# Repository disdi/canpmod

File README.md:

# CAN PMOD

CAN PMOD is a 3.3 V SN65HVD230 CAN transceiver module, based on the
[Waveshare SN65HVD230 CAN board](https://www.waveshare.com/sn65hvd230-can-board.htm/).
The host must provide the CAN protocol controller.

The project is **KiCad 9.0.8**. Open [kicad/canpmod.kicad_pro](kicad/canpmod.kicad_pro).
The two-layer, 1.6 mm board has 12 components and keeps its original outline
and component placement.

This revision corrects the PMOD footprint's physical numbering, reroutes the
affected nets, adds local connector footprints, and refreshes silkscreen and
library symbols. ERC reports 0 errors and 0 warnings. DRC with schematic
parity reports 0 violations and 0 unconnected items.

The photographs above show the original board. They remain in `img/` as
historical images.

## PMOD connections

**J2** is the right-angle male PMOD header. Viewed from the PCB top with its
plug pointing left, pins 1–6 run top to bottom in the inboard row; pins 7–12
run top to bottom in the outboard row. Pin 1 is square and marked on silkscreen.

| PMOD pin | Signal | Function |
| --- | --- | --- |
| 1 | NC | Unconnected |
| 2 | NC | Unconnected |
| 3 | NC | Unconnected |
| 4 | CAN RX | CAN receive (input to host) |
| 5 | GND | Ground |
| 6 | 3.3 V | Supply from host |
| 7 | NC | Unconnected |
| 8 | NC | Unconnected |
| 9 | NC | Unconnected |
| 10 | CAN TX | CAN transmit (output from host) |
| 11 | GND | Ground |
| 12 | 3.3 V | Supply from host |

**J1** is the 5.08 mm-pitch CAN terminal: pin 1 CAN_L, pin 2 CAN_H.
**JP1** enables the 120 Ω termination when a shunt is fitted.

R1 is the 4.7 kΩ slope-control resistor. R2 pulls TX high. C1 is the 100 nF
supply bypass. R3/C2 and R4/C3 are 100 Ω / 560 pF series RC branches from each
bus line to ground.

## Files in this revision

| Path | Role |
| --- | --- |
| [kicad/canpmod.kicad_pro](kicad/canpmod.kicad_pro) | KiCad 9 project |
| [kicad/canpmod.kicad_sch](kicad/canpmod.kicad_sch) | Schematic |
| [kicad/canpmod.kicad_pcb](kicad/canpmod.kicad_pcb) | Board |
| [kicad/fp-lib-table](kicad/fp-lib-table) | Local footprint table (`${KIPRJMOD}`) |
| [kicad/libs/canpmod.pretty/PMOD_2x06_Horizontal.kicad_mod](kicad/libs/canpmod.pretty/PMOD_2x06_Horizontal.kicad_mod) | Corrected PMOD 2×6 land |
| [kicad/libs/canpmod.pretty/TerminalBlock_bornier-2_P5.08mm.kicad_mod](kicad/libs/canpmod.pretty/TerminalBlock_bornier-2_P5.08mm.kicad_mod) | 5.08 mm CAN terminal land |
| [kicad/output_files/BOM-canpmod.csv](kicad/output_files/BOM-canpmod.csv) | BOM, 12 components |
| [kicad/output_files/CPL-canpmod.csv](kicad/output_files/CPL-canpmod.csv) | Pick-and-place |
| [kicad/output_files/gerbers/](kicad/output_files/gerbers/) | Gerbers and drill for this board |

`kicad/output_files/GERBER-canpmod.zip` is the earlier KiCad 7 Gerber package.
Use the `gerbers/` directory for the KiCad 9 board.

J2 needs a manufactured right-angle 2×6 header matched to the footprint.
Exact connector MPNs, passive ratings, assembler acceptance, and bench
validation remain open. Clean ERC/DRC is not fabrication approval.

License: [MIT, copyright 2024 disdi](LICENSE).

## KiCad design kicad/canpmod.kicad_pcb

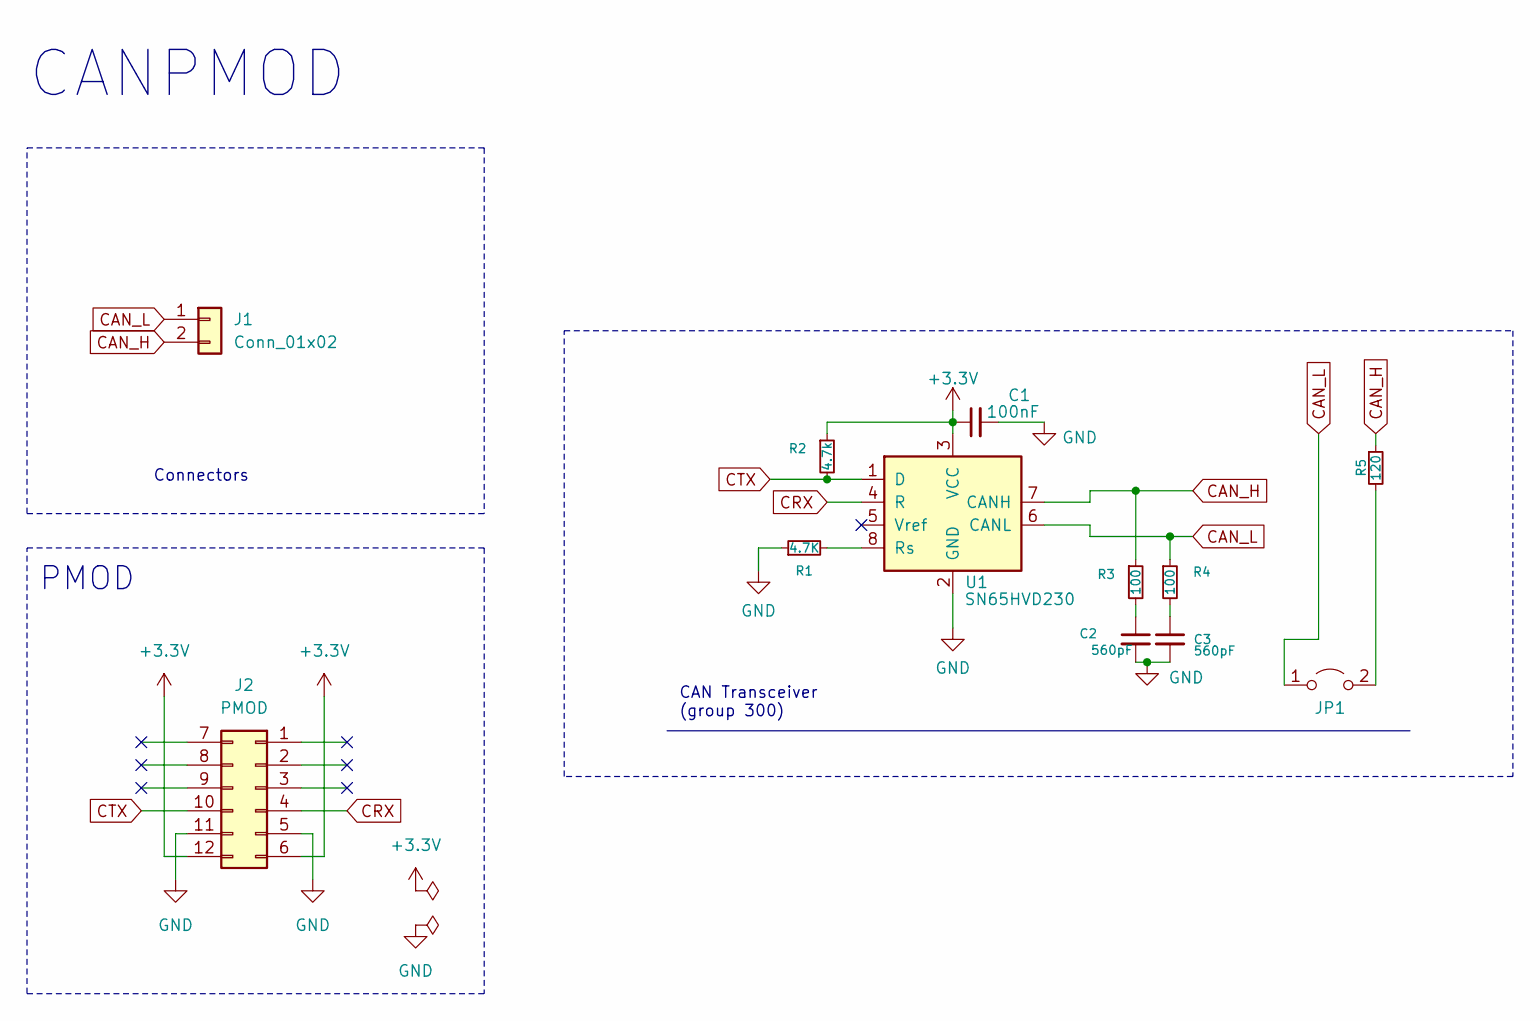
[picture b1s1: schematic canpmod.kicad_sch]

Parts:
C1: 100nF; C_0603_1608Metric
C2, C3: 560pF; C_0603_1608Metric
J1: Conn_01x02; TerminalBlock_bornier-2_P5.08mm
J2: PMOD; PMOD_2x06_Horizontal
JP1: Jumper_2_Open; PinHeader_1x02_P2.54mm_Vertical
R1: 4.7K; R_0805_2012Metric
R2: 4.7k; R_0805_2012Metric
R3, R4: 100; R_0805_2012Metric
R5: 120; R_0603_1608Metric
U1: SN65HVD230; SOIC-8_3.9x4.9mm_P1.27mm

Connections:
+3.3V: C1.1, J2.6, J2.12, R2.1, U1.3 (VCC)
CAN_H: J1.2, R3.1, R5.1, U1.7 (CANH)
CAN_L: J1.1, JP1.1 (A), R4.1, U1.6 (CANL)
CRX: J2.4, U1.4 (R)
CTX: J2.10, R2.2, U1.1 (D)
GND: C1.2, C2.2, C3.2, J2.5, J2.11, R1.1, U1.2 (GND)
unnamed: C2.1, R3.2
unnamed: C3.1, R4.2
unnamed: JP1.2 (B), R5.2
unnamed: R1.2, U1.8 (Rs)

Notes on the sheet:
CAN Transceiver (group 300)
PMOD
Connectors
CANPMOD

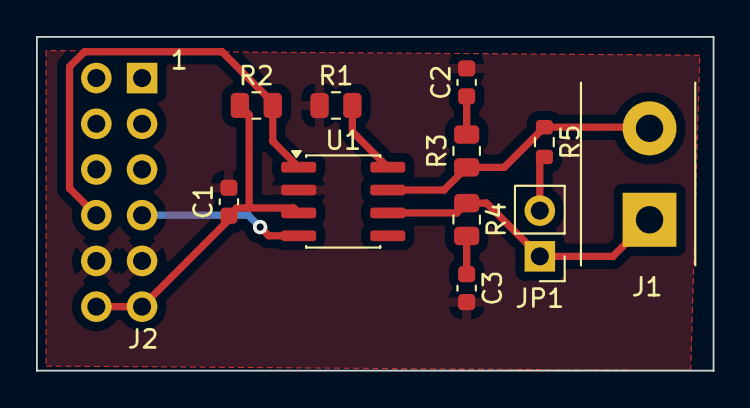
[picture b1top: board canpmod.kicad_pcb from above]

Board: 2 copper layers, 37.6 x 18.5 mm, 12 parts (0 on the bottom side), 10 nets.

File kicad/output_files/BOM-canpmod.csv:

Comment,Designator,Footprint,LCSC
100nF,C1,Capacitor_SMD:C_0603_1608Metric,
560pF,C2,Capacitor_SMD:C_0603_1608Metric,
560pF,C3,Capacitor_SMD:C_0603_1608Metric,
Conn_01x02,J1,canpmod:TerminalBlock_bornier-2_P5.08mm,
PMOD,J2,canpmod:PMOD_2x06_Horizontal,
Jumper_2_Open,JP1,Connector_PinHeader_2.54mm:PinHeader_1x02_P2.54mm_Vertical,
4.7K,R1,Resistor_SMD:R_0805_2012Metric,
4.7k,R2,Resistor_SMD:R_0805_2012Metric,
100,R3,Resistor_SMD:R_0805_2012Metric,
100,R4,Resistor_SMD:R_0805_2012Metric,
120,R5,Resistor_SMD:R_0603_1608Metric,
SN65HVD230,U1,Package_SO:SOIC-8_3.9x4.9mm_P1.27mm,

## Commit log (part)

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2024-01-07 Add Kicad files for CAN PMOD
2024-01-07 Update image and Readme
2024-01-11 Improve routing and add 3d image
